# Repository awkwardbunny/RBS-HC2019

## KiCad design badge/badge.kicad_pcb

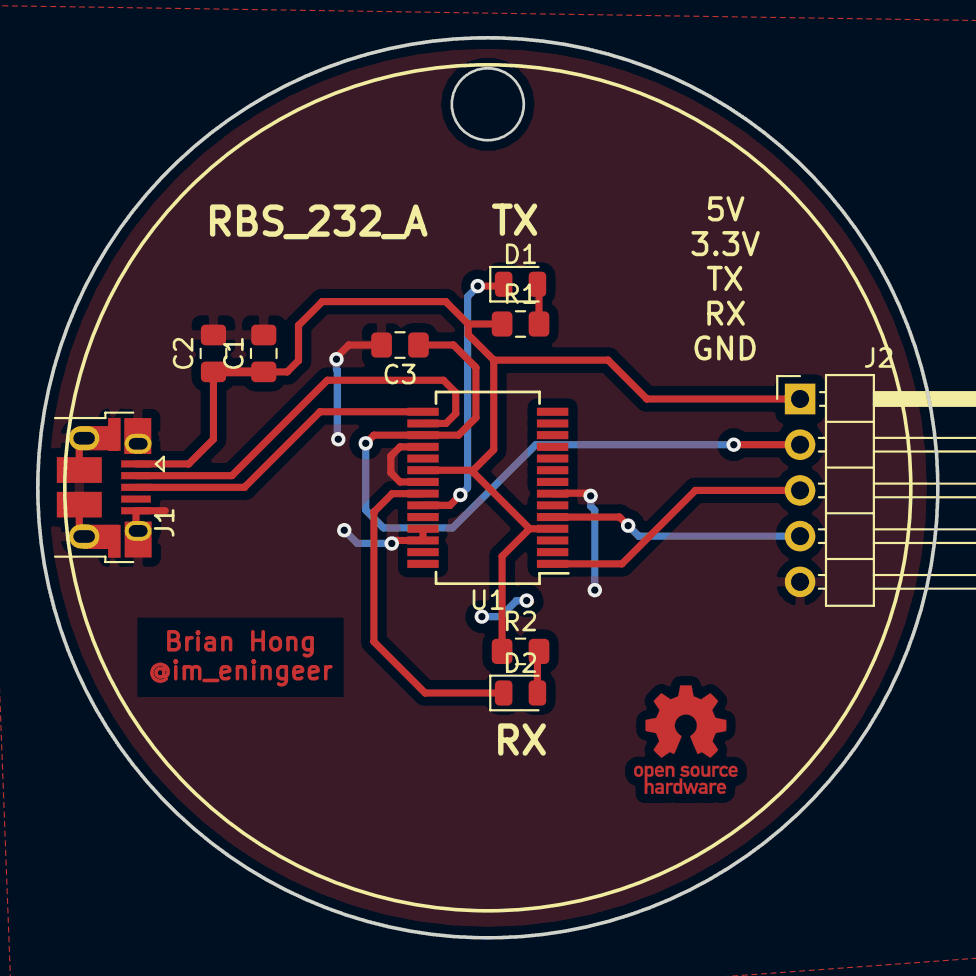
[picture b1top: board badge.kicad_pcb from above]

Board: 2 copper layers, 50.0 x 50.0 mm, 10 parts (0 on the bottom side), 11 nets.

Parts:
C1: 10n; C_0805_2012Metric_Pad1.15x1.40mm_HandSolder
C2, C3: 100n; C_0805_2012Metric_Pad1.15x1.40mm_HandSolder
D1: LED_TX; LED_0805_2012Metric
D2: LED_RX; LED_0805_2012Metric
J1: USB_B_Micro; USB_Micro-B_Amphenol_10103594-0001LF_Horizontal
J2: Conn_01x05; PinHeader_1x05_P2.54mm_Horizontal
R1, R2: 270; R_0805_2012Metric_Pad1.15x1.40mm_HandSolder
U1: FT232RL; SSOP-28_5.3x10.2mm_P0.65mm

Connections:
GND: C1.2, C2.2, C3.2, J1.5, J1.6, J2.5, U1.7, U1.18, U1.21, U1.25, U1.26
unnamed: C1.1, C2.1, J1.1, J2.1, R1.1, R2.1, U1.4, U1.20
unnamed: C3.1, J2.2, U1.17
unnamed: D1.1, U1.23
unnamed: D1.2, R1.2
unnamed: D2.1, U1.22
unnamed: D2.2, R2.2
unnamed: J1.2, U1.16
unnamed: J1.3, U1.15
unnamed: J2.3, U1.1
unnamed: J2.4, U1.5

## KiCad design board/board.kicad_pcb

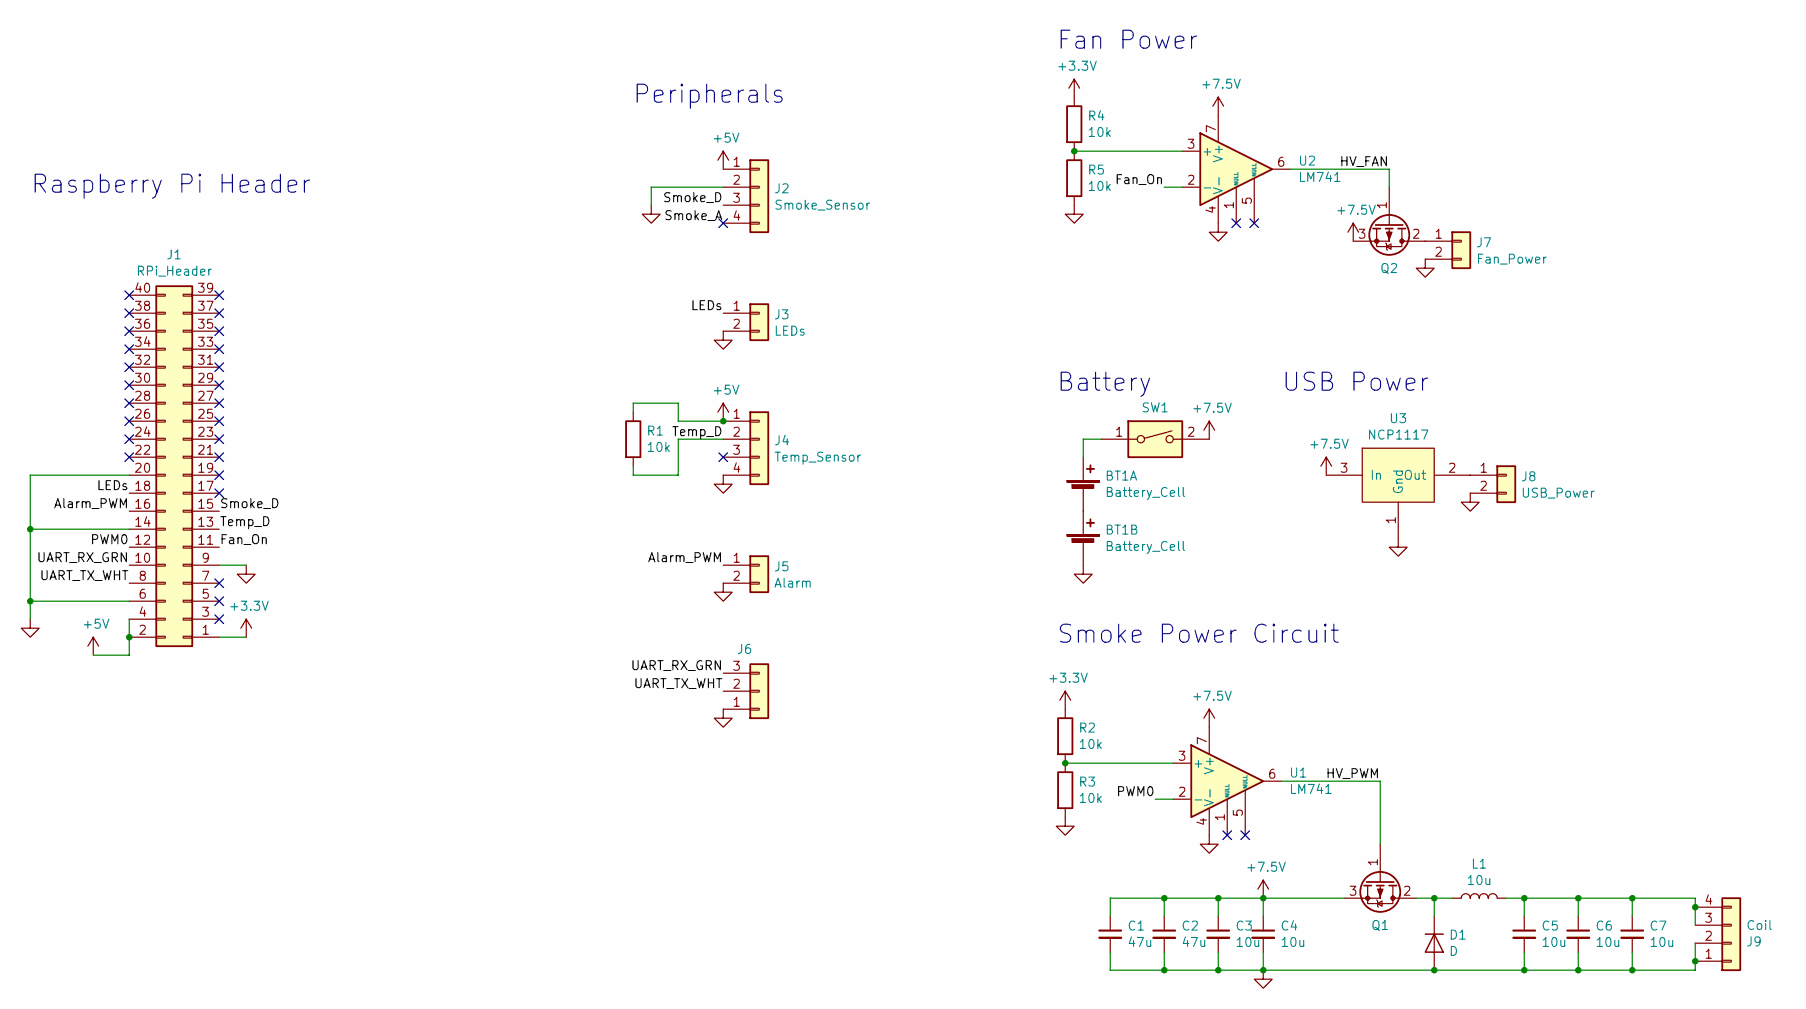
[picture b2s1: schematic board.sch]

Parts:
BT1: Battery_Cell; Keystone_1048_2x18650
C1, C2: 47u; C_0805_2012Metric_Pad1.15x1.40mm_HandSolder
C3, C4, C5, C6, C7: 10u; C_0805_2012Metric_Pad1.15x1.40mm_HandSolder
D1: D; D_DO-41_SOD81_P7.62mm_Horizontal
J1: RPi_Header; PinHeader_2x20_P2.54mm_Vertical
J2: Smoke_Sensor; PinHeader_1x04_P2.54mm_Horizontal
J3: LEDs; PinHeader_1x02_P2.54mm_Horizontal
J4: Temp_Sensor; PinHeader_1x04_P2.54mm_Horizontal
J5: Alarm; PinHeader_1x02_P2.54mm_Horizontal
J6: Conn_01x03; PinHeader_1x03_P2.54mm_Horizontal
J7: Fan_Power; PinHeader_1x02_P2.54mm_Horizontal
J8: USB_Power; PinHeader_1x02_P2.54mm_Vertical
J9: Coil; PinHeader_1x04_P2.54mm_Horizontal
L1: 10u; L_Wuerth_HCI-1365
Q1, Q2: Q_PMOS_GDS; TO-252-2
R1, R2, R3, R4, R5: 10k; R_0805_2012Metric_Pad1.15x1.40mm_HandSolder
SW1: SW_DIP_x01; SW_DIP_SPSTx01_Slide_6.7x4.1mm_W7.62mm_P2.54mm_LowProfile
U1, U2: LM741; DIP-8_W7.62mm_Socket_LongPads
U3: NCP1117; SOT-223-3_TabPin2

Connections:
+3V3: J1.1, R2.1, R4.1
+5V: J1.2, J1.4, J2.1, J4.1, R1.1
+7.5V: C1.1, C2.1, C3.1, C4.1, Q1.3 (S), Q2.3 (S), SW1.2, U1.7 (V+), U2.7 (V+), U3.3 (In)
/Alarm_PWM: J1.16, J5.1
/Fan_On: J1.11, U2.2 (-)
/HV_FAN: Q2.1 (G), U2.6
/HV_PWM: Q1.1 (G), U1.6
/LEDs: J1.18, J3.1
/PWM0: J1.12, U1.2 (-)
/Smoke_A: J2.4
/Smoke_D: J1.15, J2.3
/Temp_D: J1.13, J4.2, R1.2
/UART_RX_GRN: J1.10, J6.3
/UART_TX_WHT: J1.8, J6.2
GND: BT1.3 (-), C1.2, C2.2, C3.2, C4.2, C5.2, C6.2, C7.2, D1.2 (A), J1.6, J1.9, J1.14, J1.20, J2.2, J3.2, J4.4, J5.2, J6.1, J7.2, J8.2, J9.1, J9.2, R3.2, R5.2, U1.4 (V-), U2.4 (V-), U3.1 (Gnd)
unnamed: BT1.1 (+), SW1.1
unnamed: BT1.2 (-), BT1.4 (+)
unnamed: C5.1, C6.1, C7.1, J9.3, J9.4, L1.2
unnamed: D1.1 (K), L1.1, Q1.2 (D)
unnamed: J7.1, Q2.2 (D)
unnamed: J8.1, U3.2 (Out)
unnamed: R2.2, R3.1, U1.3 (+)
unnamed: R4.2, R5.1, U2.3 (+)

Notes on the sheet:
Smoke Power Circuit
USB Power
Battery
Fan Power
Raspberry Pi Header
Peripherals

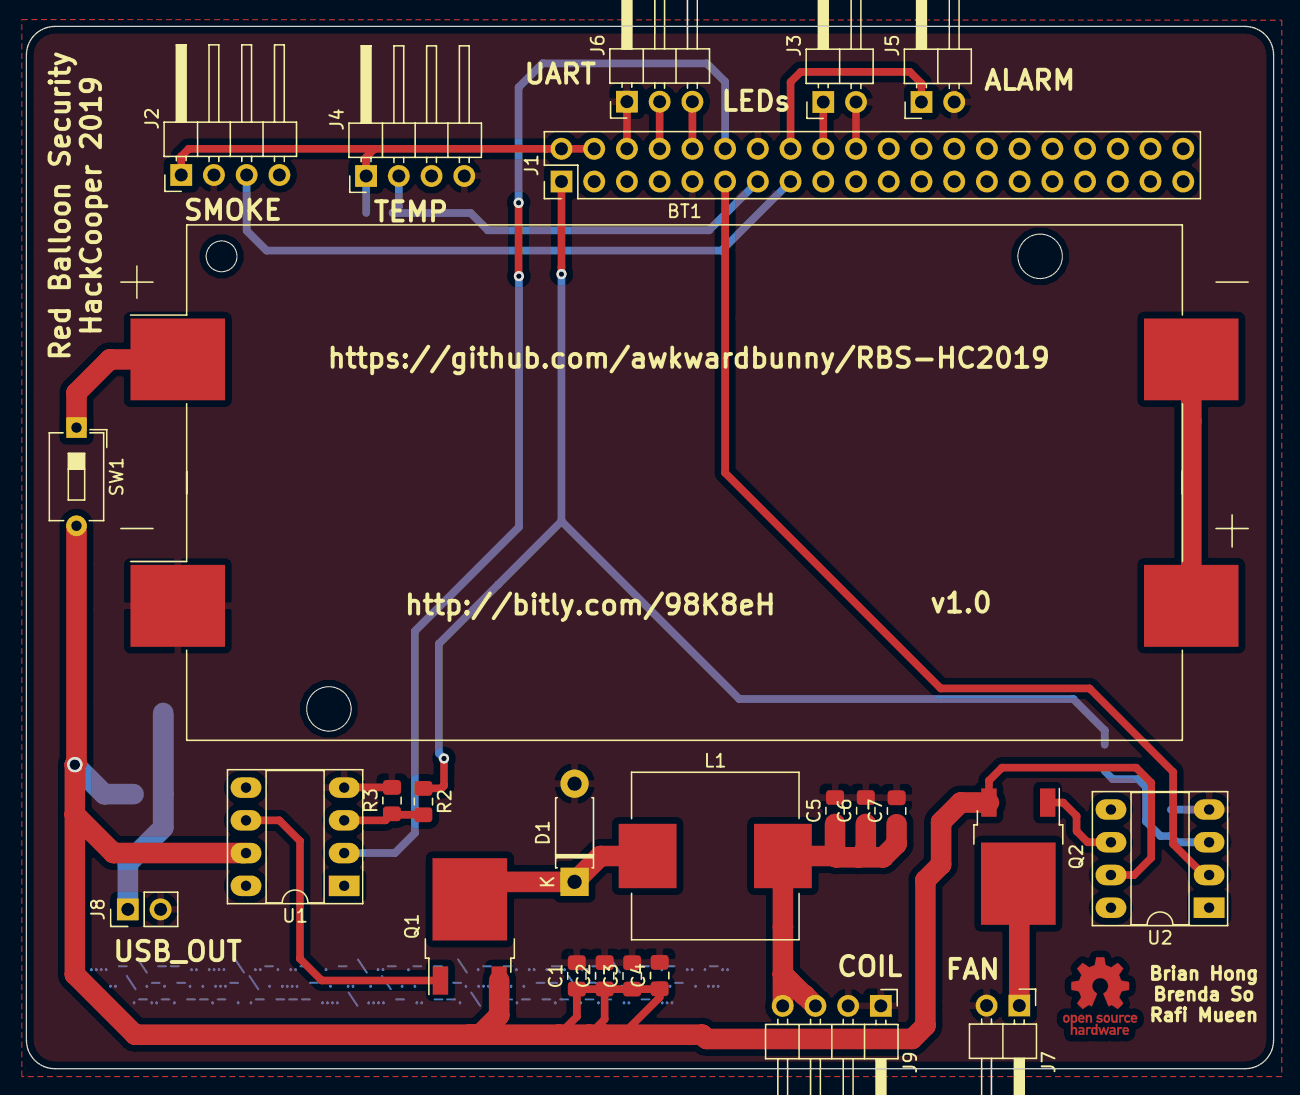
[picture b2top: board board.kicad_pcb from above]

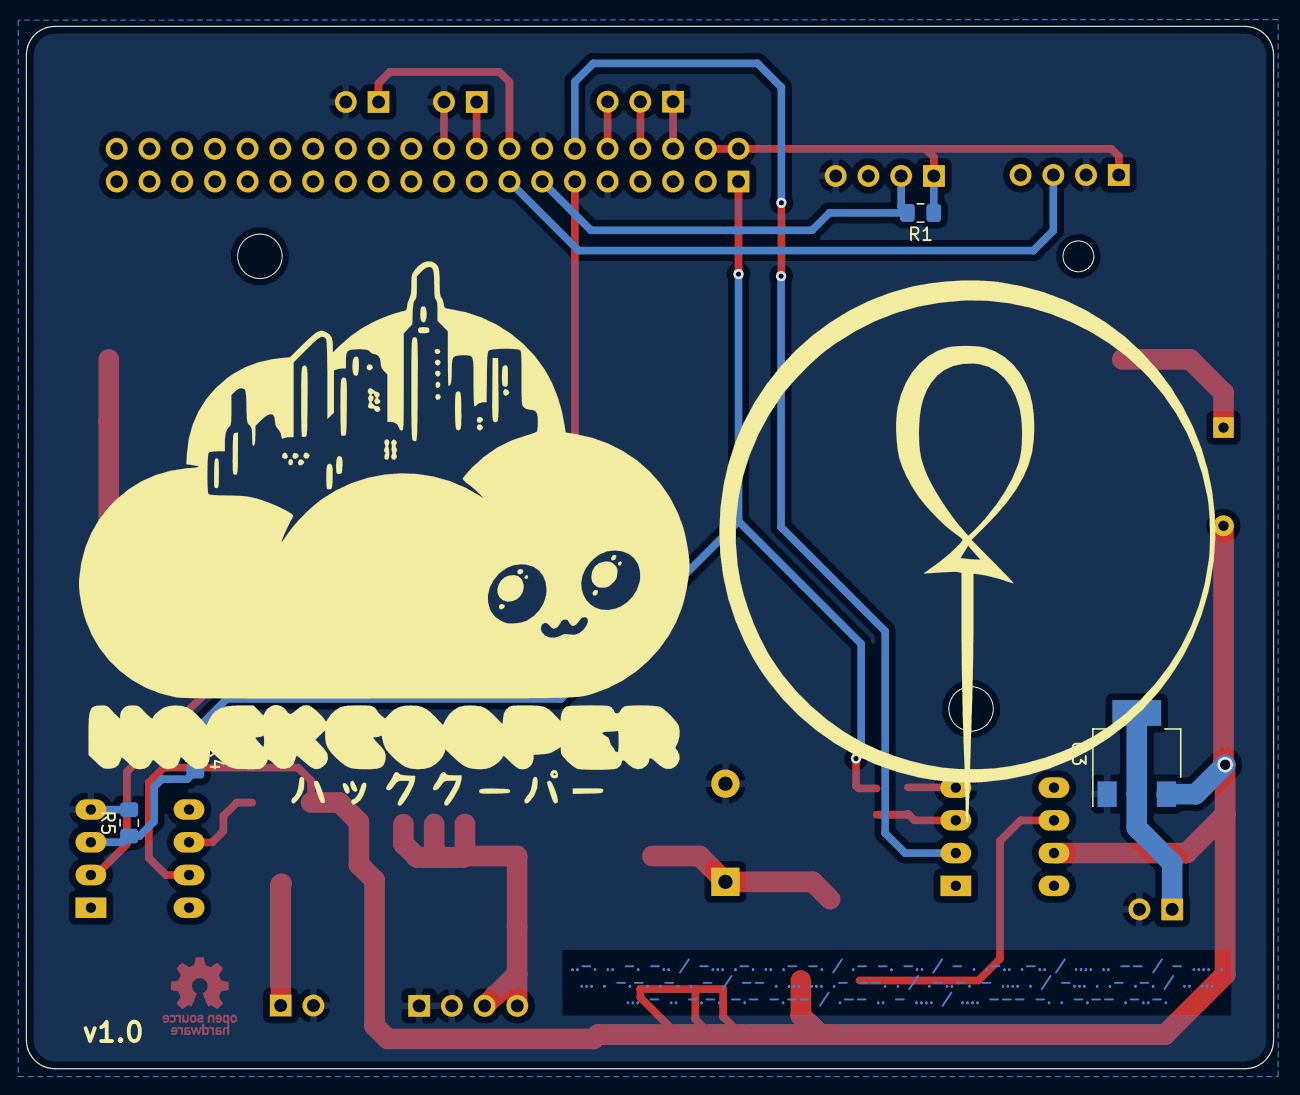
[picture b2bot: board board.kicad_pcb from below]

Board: 2 copper layers, 96.8 x 80.9 mm, 30 parts (4 on the bottom side), 22 nets.

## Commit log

2019-08-20 Add symbol for 2x18650 battery holder
2019-08-20 Finished
2019-08-21 Fixed hole in battery footprint
2019-08-21 Added labels
2019-08-21 Rounded corners (edge cuts + zone fill)
2019-08-21 Custom badge
2019-08-21 Fixed and panelized
    Added text to RS232 board
    Added on/off switch to main board
2019-08-22 Thicker tabs for JLCPCB (>3mm)
2019-09-03 Output (not sure what changed)
2019-09-03 Format page and schematic.pdf
